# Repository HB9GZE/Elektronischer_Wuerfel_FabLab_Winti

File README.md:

# Elektronischer_Wuerfel_FabLab_Winti
Schematics, Layout, BOM, 3D Print-files and Software to buiold an "Electronic Dice"

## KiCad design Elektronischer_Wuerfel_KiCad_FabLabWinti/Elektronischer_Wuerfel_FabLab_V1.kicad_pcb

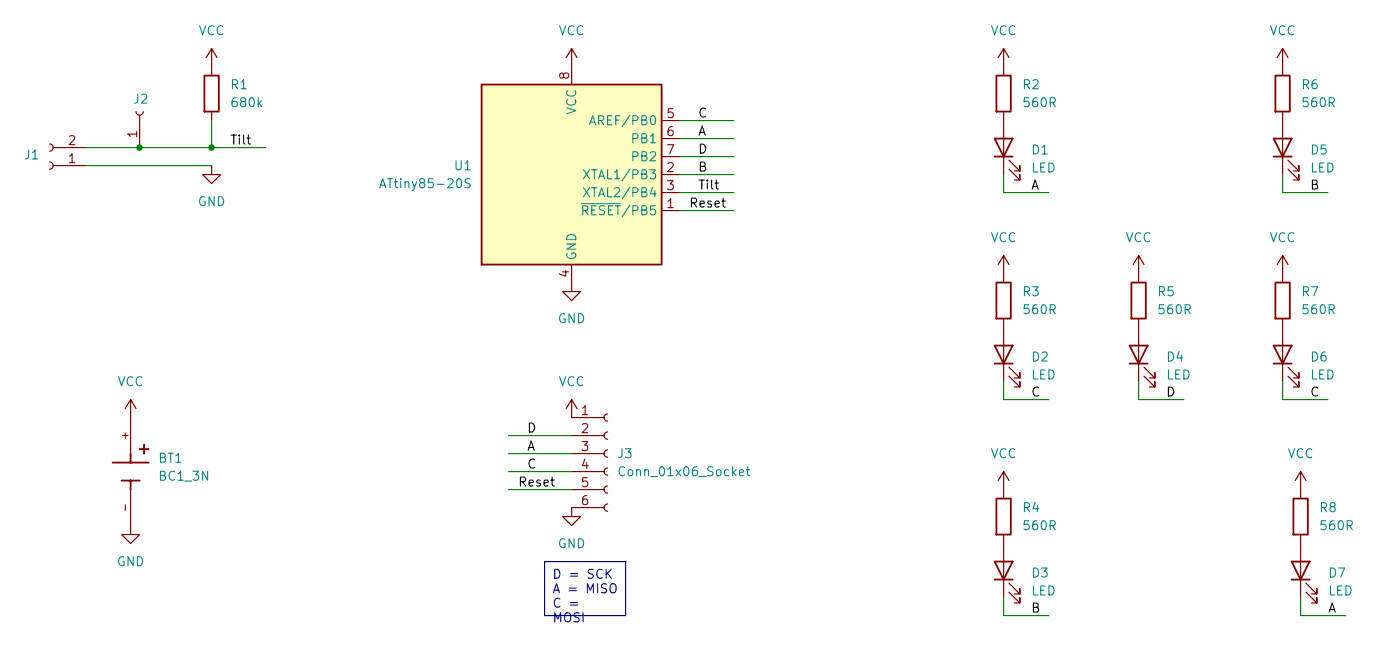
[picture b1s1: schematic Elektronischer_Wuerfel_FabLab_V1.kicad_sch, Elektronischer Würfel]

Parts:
BT1: BC1_3N; BAT_BC1_3N
D1, D2, D3, D4, D5, D6, D7: LED; LED_0805_2012Metric_Pad1.15x1.40mm_HandSolder
J1: Conn_01x02_Socket; PinHeader_1x02_P2.00mm_Vertical
J2: Conn_01x01_Socket; PinHeader_1x01_P2.00mm_Vertical
J3: Conn_01x06_Socket; PinHeader_1x06_P1.27mm_Vertical
R1: 680k; R_0603_1608Metric_Pad0.98x0.95mm_HandSolder
R2, R3, R4, R5, R6, R7, R8: 560R; R_0603_1608Metric_Pad0.98x0.95mm_HandSolder
U1: ATtiny85-20S; SOIC-8W_5.3x5.3mm_P1.27mm

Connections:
/A: D1.1 (K), D7.1 (K), J3.3, U1.6 (PB1)
/B: D3.1 (K), D5.1 (K), U1.2 (XTAL1/PB3)
/C: D2.1 (K), D6.1 (K), J3.4, U1.5 (AREF/PB0)
/D: D4.1 (K), J3.2, U1.7 (PB2)
/Reset: J3.5, U1.1 (~RESET/PB5)
/Tilt: J1.2, J2.1, R1.2, U1.3 (XTAL2/PB4)
GND: BT1.-, J1.1, J3.6, U1.4 (GND)
unnamed: D1.2 (A), R2.2
unnamed: D2.2 (A), R3.2
unnamed: D3.2 (A), R4.2
unnamed: D4.2 (A), R5.2
unnamed: D5.2 (A), R6.2
unnamed: D6.2 (A), R7.2
unnamed: D7.2 (A), R8.2
VCC: BT1.+, J3.1, R1.1, R2.1, R3.1, R4.1, R5.1, R6.1, R7.1, R8.1, U1.8 (VCC)

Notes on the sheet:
D = SCK A = MISO C = MOSI

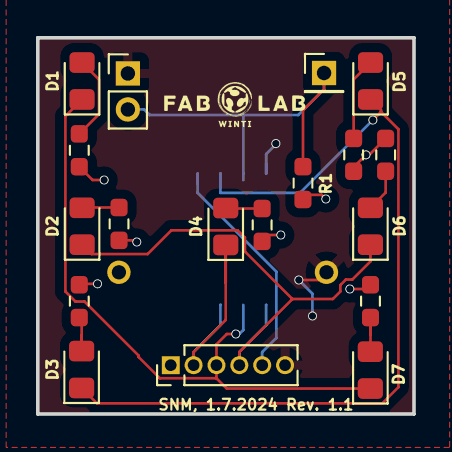
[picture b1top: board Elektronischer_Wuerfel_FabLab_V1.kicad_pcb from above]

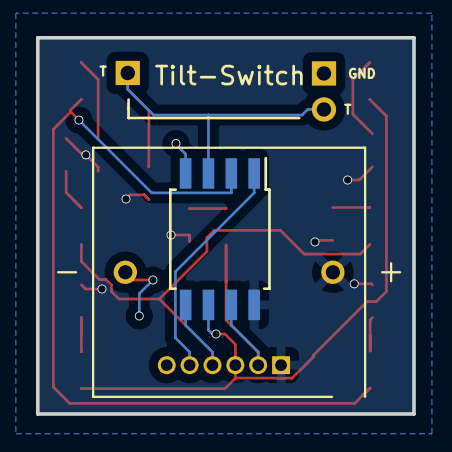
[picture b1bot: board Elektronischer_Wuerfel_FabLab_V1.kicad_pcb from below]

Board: 2 copper layers, 20.9 x 20.9 mm, 20 parts (2 on the bottom side), 15 nets.

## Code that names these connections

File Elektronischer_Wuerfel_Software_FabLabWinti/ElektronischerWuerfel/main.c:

/*
 * Elektronischer Wuerfel V1.1
 * (kleine Version)
 *
 * Created: 17.02.2016 15:20:19
 * Author : rags
 */

#define PATTERN1

#include <avr/io.h>
#include <util/delay.h>
#include <avr/interrupt.h>
#include <avr/sleep.h>
#include <avr/power.h>

/* Funktionsprototypen */
void enterSleep();
void One();
void Two();
void Three();
void Four();
void Five();
void Six();
void Pat1();
void Pat2();
void Pat3();
void LEDoff();

/* Bits setzen (sbi) und löschen (cbi) */
#ifndef cbi
#define cbi(sfr, bit) (_SFR_BYTE(sfr) &= ~_BV(bit))
#endif
#ifndef sbi
#define sbi(sfr, bit) (_SFR_BYTE(sfr) |= _BV(bit))
#endif

/* Inputs & Outputs */
#define led_A      1             // IC Pin6, PB1, output
#define led_B      3             // IC Pin2, PB3, output
#define led_C      0             // IC Pin5, PB0, output
#define led_D      2             // IC Pin7, PB2, output
#define buttonPin  4             // IC Pin3, PB4, input

/* Defines */
#define TIMEOUT_DISPLAY   500       // Timeout-Variable während dem Anzeigen der gewürfelten Zahl
#define TIMEOUT_SHUFFLE   5000      // Timeout-Variable während dem Würfeln

#define TIME_ON		5				// Zeitanteil von 10ms, in dem die LED eingeschaltet ist (Dimming)
#define TIME_OFF	5				// Zeitanteil von 10ms, in dem die LED ausgeschaltet ist (Dimming)


/* Variablen */
volatile char buttonState;					// Speichervariable für den Zustand des Kippschalters
volatile unsigned char dicecnt = 0;			// Zählvariable für die Zufallszahl (Wertebereich 0...5)
volatile unsigned int timeoutCnt_disp;		// Zählvariable für Timeout während dem Anzeigen der gewürfelten Zahl
volatile unsigned int timeoutCnt_shuf;		// Zählvariable für Timeout während dem Würfeln
volatile unsigned char dispcount = 0;		// Zählvariable für Timeout während dem Würfeln
volatile unsigned char count = 0;			// Zählvariable für Timeout während dem Würfeln

/* Einen Zeiger erstellen, der auf ein Array mit Funktionen (Anzeige Zahlen 1..6) zeigt */
typedef void (* NumFuncPTR) ();
NumFuncPTR ShowNumber[6] = {One,Two,Three,Four,Five,Six};
/* Würfelmuster definieren, das beim Würfeln angezeigt wird */
#ifdef PATTERN1
	NumFuncPTR ShowPattern[8] = {Pat1,Pat2,One,Pat2,Pat3,Pat2,One,Pat2};
#endif
#ifdef PATTERN2
	NumFuncPTR ShowPattern[8] = {Pat1,Pat2,Pat3,Pat2,Pat1,Pat2,Pat3,Pat2};
#endif
#ifdef PATTERN3
	NumFuncPTR ShowPattern[8] = {One,Six,LEDoff,LEDoff,One,Six,LEDoff,LEDoff};
#endif

void setup() {
	/* Ungenutzte Funktionen ausschalten -> Batterieverbrauch optimieren! */
	power_adc_disable();          // Analog/Digital-Wandler ausschalten
	power_usi_disable();          // Serielle Schnittstelle ausschalten
	power_timer1_disable();       // Timer 1 ausschalten
	
	/* Port B konfigurieren: 0 = input, 1 = output */
	DDRB |= (1 << led_A);
	DDRB |= (1 << led_B);
	DDRB |= (1 << led_C);
	DDRB |= (1 << led_D);
	DDRB &= ~(1 << buttonPin);
	
	/* Timeout-Variablen zurücksetzen */
	timeoutCnt_disp = 0;
	timeoutCnt_shuf = 0;
}


int main(void) {
	
	setup();
	
    while (1) {
	
		/* Einlesen des Kippschalters */
		buttonState = (PINB >> buttonPin) & 1;
	
		timeoutCnt_shuf = 0;
		
		/* Solange der Würfel gekippt wird, wird die folgende Schleife nicht verlassen: */
		while(buttonState == 0) {
			
			/* Aktuellen Zeitstempel in Variable speichern */
			timeoutCnt_disp = 0;
			
			/* Zeitverzögerung in ms, welche die Zählgeschwindigkeit regelt */
		
			timeoutCnt_shuf++;
			
			/* Zählervariable um 1 erhöhen. Wenn sie 5 erreicht hat, wieder nullsetzen */
			if (dicecnt < 5) dicecnt++;
			else dicecnt = 0;
			
			/* Teiler / 73 */
			if (count < 73) count++;
			else {
				count = 0;
				if (dispcount < 7) dispcount++;
				else dispcount = 0;
			}
			
			/* Zählmuster anzeigen */
			ShowPattern[dispcount]();
			/* LED's nur xx% der Zeit einschalten -> Batterieverbrauch optimieren */
			_delay_ms(0.1*TIME_ON);
			LEDoff();
			_delay_ms(0.1*TIME_OFF);

			/* Einlesen des Kippschalters */
			buttonState = (PINB >> buttonPin) & 1;
			
			/* Nach einer bestimmten Zeit wird der Würfel abgeschaltet -> Batterieverbrauch! */
			if (timeoutCnt_shuf > TIMEOUT_SHUFFLE) {
				LEDoff();
				enterSleep();
			}

		}
		
		/* Gewürfelte Zahl mit den LED anzeigen */
		ShowNumber[dicecnt]();
		/* LED's nur xx% der Zeit einschalten -> Batterieverbrauch optimieren */
		_delay_ms(TIME_ON);
		LEDoff();
		_delay_ms(TIME_OFF);
		/* Timeout-Variable inkrementieren */
		timeoutCnt_disp++;
			
		/* Nach einer bestimmten Zeit wird der Würfel abgeschaltet -> Batterieverbrauch! */
		if (timeoutCnt_disp > TIMEOUT_DISPLAY){
			LEDoff();
			enterSleep();
		}
		
    }
}


void enterSleep() {

	sbi(GIMSK,PCIE);                          // Pin-Change-Interrupt einschalten
	sbi(PCMSK,PCINT4);                        // Pin-Change-Eingang definieren (ATtiny: IC Pin3,PB4)
	
	set_sleep_mode(SLEEP_MODE_PWR_DOWN);
	cli();
	sleep_enable();
	sleep_bod_disable();
	sei();
	sleep_cpu();
	
	/* ------------------------------------------------------------------------------------------- */
	/* uC befindet sich im Sleep Mode. Nach dem Kippen des Würfels wird der Code hier fortgesetzt! */
	/* ------------------------------------------------------------------------------------------- */

	sleep_disable();
	cli();
	
	/* Ungenutzte Funktionen ausschalten -> Batterieverbrauch optimieren! */
	power_adc_disable();
	power_usi_disable();
	power_timer1_disable();
}


/* Ist der Würfel im Sleep Mode und wird gekippt, so wird ein Interrupt mit dieser Interruptroutine ausgelöst */
ISR(PCINT0_vect) {
	unsigned char tempButtonState1 = (PINB >> buttonPin) & 1;
	/* SW-Entprellung: 50ms (verhindert das Würfeln z.B. bei Vibrationen)*/
	_delay_ms(50);
	unsigned char tempButtonState2 = (PINB >> buttonPin) & 1;
	if (tempButtonState1 != tempButtonState2) enterSleep();
}

/* ---------------------------------------------- */
/*  Funktionen zur Anzeige der gewürfelten Zahlen */
/* ---------------------------------------------- */

void One(){
	PORTB = 0b00001011;
};
void Two(){
	PORTB = 0b00001101;
};
void Three(){
	PORTB = 0b00001001;
};
void Four(){
	PORTB = 0b00000101;
};
void Five(){
	PORTB = 0b00000001;
};
void Six(){
	PORTB = 0b00000100;
};
void Pat1(){
	PORTB = 0b00001101;
};
void Pat2(){
	PORTB = 0b00001110;
};
void Pat3(){
	PORTB = 0b00000111;
};
void LEDoff(){
	PORTB = 0b00001111;
}

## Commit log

2024-02-13 Adding files
    Initial upload
2024-07-13 edit BOM list
2024-07-14 some minor changes, repair of not connected A
2024-07-14 Moved tilt switch a bit to give more space at the board edge.
2024-07-22 added software and stl directories into the project
2024-07-22 changed directory name of KiCad private library
2024-08-26 minor stuff I think ;-)
